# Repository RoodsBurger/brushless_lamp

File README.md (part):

# Brushless Lamp

Kinetic smart lamp. A BLDC gimbal motor raises / lowers a lit core to control
brightness; CCT LEDs ride with the core. A single rotary-encoder knob with push-
button drives everything locally; Matter over WiFi exposes the lamp to Apple
Home / Google Home / SmartThings. Production hardware is the **Seeed XIAO
ESP32-S3** running ESP-IDF + esp-matter; the chip handles the SimpleFOC v2.4.0
FOC loop itself on a dedicated core while WiFi, BLE, and CHIP share the other.

## Production build → [`s3/README.md`](s3/README.md)

That doc is the source of truth for everything current: BOM, wiring, toolchain,
build + flash, per-device Matter provisioning, code architecture, troubleshooting,
and the diagnostic story for the external-5 V boot path (see § 7.1). Start there.

## Repo layout

```
s3/                  Current build (XIAO ESP32-S3 + esp-matter)
  ├── firmware/      PRODUCTION — Matter ColorTemperatureLight
  ├── common/        Shared motor / pins / config
  ├── components/    Vendored SimpleFOC v2.4.0
  └── archive/       Dev history + diagnostic targets (none ship)
esp-idf/             Historical (XIAO ESP32-C6 build, frozen for rollback)
```

The C6 build below is kept verbatim only as a rollback reference.

---

## Historical (XIAO ESP32-C6, frozen for rollback)

The original BrushlessLamp build targeted the XIAO ESP32-C6 with arduino-esp32's
Matter library on top. It works, but Matter on C6 had several upstream bugs
(WiFi-reconnect crash, shared-default QR codes, etc.) that drove the migration
to the S3 + esp-matter stack documented in `s3/README.md`. The sections below
describe that older build and remain accurate for `esp-idf/`.

### Milestones — M1 + M2 + M3a + M3b + M4

Closed-loop **angular-position control** on the motor via an MT6701 ABZ encoder. A rotary encoder knob with push-button drives the user interface:
- **Position mode (default)**: knob turns the motor — the lit core rises/falls mechanically. Commanded position at 0 electrically turns the LEDs **off**.
- **Brightness mode**: knob adjusts LED brightness 0–100 % on a logarithmic curve.
- **Single click**: toggle between position and brightness mode.
- **Double click**: cycle motor speed preset `{10, 15, 20, 25}` rad/s.
- **Long-hold 5 s**: lamp LEDs pulse 5× as factory-reset warning.
- **Long-hold 9 s**: factory reset (clears Preferences, reboots).

`commanded`, `speed_idx`, `brightness`, and `cct` persist in flash. Boot applies a sensor_offset so the motor doesn't jump on startup.

### Hardware

- **MCU:** Seeed Studio XIAO ESP32-C6 (RISC-V, single HP core, WiFi 6, BLE 5, 802.15.4 for later Matter-over-Thread)
- **Driver:** SimpleFOC Mini (DRV8313; 3-phase, `IN1`/`IN2`/`IN3`/`EN` + `nSLEEP`/`nFAULT` + `U`/`V`/`W` phases)
- **Motor:** 4015 BLDC gimbal, 12–36 V, 11 pole pairs, hollow-shaft external rotor
- **Motor encoder:** MT6701 (ABZ mode, 1024 CPR)
- **User input:** PEC11-style rotary encoder with integrated push-button (20 detents/rev)
- **LED strip:** dual-channel CCT (common anode + warm-white cathode + cool-white cathode), driven at 24 V
- **LED switching:** 2× AO3400A N-channel logic-level MOSFETs (SOT-23), one per channel
- **Power:** Mean Well LRS-75-24 (24 V 3.2 A)
- **Buck:** Mini360 24 V → 5 V for the MCU

### Wiring

PWM + nSLEEP on D7–D10 (driver cluster), motor encoder A/B on D0/D1, rotary knob + push-button on D2–D4, LED MOSFET gates on D5/D6. All 11 broken-out GPIOs are used. EN is **hard-tied to 3V3 on the SimpleFOC Mini itself** — its pull-up is too weak to survive a floating MCU pin, and a lamp doesn't need software tri-state (`motor.disable()` still drives all three phases to 50 % duty, zero phase-to-phase differential, zero torque). nFAULT and Z are intentionally unconnected: stall detection covers faults, and Z only helps for single-turn absolute positioning which this project doesn't need.

| XIAO pin | Chip GPIO | Target | Notes |
|---|---|---|---|
| D10 | GPIO 18 | SimpleFOC Mini IN1 | PWM phase A (MCPWM) |
| D9  | GPIO 20 | SimpleFOC Mini IN2 | PWM phase B (MCPWM) |
| D8  | GPIO 19 | SimpleFOC Mini IN3 | PWM phase C (MCPWM) |
| D7  | GPIO 17 | SimpleFOC Mini nSLEEP | pulse LOW ≥ 30 µs to clear latched OCP/TSD |
| D6  | GPIO 16 | LED CW MOSFET gate | LEDC PWM 25 kHz, 10-bit |
| D5  | GPIO 23 | LED WW MOSFET gate | LEDC PWM 25 kHz, 10-bit |
| D0  | GPIO 0  | MT6701 A | quadrature, internal pull-up |
| D1  | GPIO 1  | MT6701 B | quadrature, internal pull-up |
| D2  | GPIO 2  | Rotary encoder A | PCNT ch0, hardware glitch-filtered |
| D3  | GPIO 21 | Rotary encoder B | PCNT ch1, hardware glitch-filtered |
| D4  | GPIO 22 | Rotary push button | INPUT_PULLUP, polled |
| 3V3 | — | MT6701 V+ · SimpleFOC Mini 3V3 · **EN jumper** · rotary encoder V+ | sourced from the XIAO's onboard LDO |
| GND | — | GND | common with Mean Well V−, Mini360 OUT−, and both LED MOSFET sources |
| 5V  | — | Mini360 OUT+ | XIAO power; onboard LDO then drives the 3V3 rail |
| — | — | Mean Well 24 V → Mini VCC / VM · LED strip VCC | motor rail + LED rail (shared 24 V) |

**Install a jumper from 3V3 to the EN header on the SimpleFOC Mini.** This is what keeps the DRV8313 enabled; without it the driver floats disabled.

#### Peripheral wiring (complete)

**Mean Well LRS-75-24 (24 V 3.2 A, mains-powered):**
- `V+` → SimpleFOC Mini `VM`, Mini360 `IN+`
- `V−` → SimpleFOC Mini `GND`, Mini360 `IN−`, XIAO `GND` (common)
- `L` / `N` / `⏚` → mains (respect mains safety: fused, enclosed, earth the chassis)

**Mini360 buck (24 → 5 V, trim set before connecting the XIAO):**
- `IN+` → Mean Well `V+`
- `IN−` → Mean Well `V−`
- `OUT+` → XIAO `5V`
- `OUT−` → XIAO `GND`

**SimpleFOC Mini (DRV8313 breakout):**
- `VM` → Mean Well `V+`
- `GND` → common ground
- `3V3` → XIAO `3V3` (logic rail + pull-ups)
- `IN1` → XIAO `D10`
- `IN2` → XIAO `D9`
- `IN3` → XIAO `D8`
- `EN` → **jumper to `3V3`** (on the breakout itself, not to the MCU)
- `nSLEEP` → XIAO `D7`
- `nFAULT` → not connected
- `U` / `V` / `W` (screw terminals) → motor phase wires. Initial phase order is a guess — if `initFOC` fails or the motor stutters, swap any two.

**MT6701 breakout (ABZ mode — verify the mode jumper matches this; the board ships in various configurations):**
- `V+` → XIAO `3V3`
- `GND` → common ground
- `A` pad (often labelled `DO` on the breakout's dual-purpose silk) → XIAO `D0`
- `B` pad (often labelled `CLK`) → XIAO `D1`
- `Z` pad (often labelled `CS`) → not connected

**Rotary encoder (PEC11-style, 5 pins — 3 on one side for the encoder, 2 on the other for the integrated push-button):**
- Encoder pin `A` → XIAO `D2`
- Encoder pin `B` → XIAO `D3`
- Encoder common (middle of the three) → `GND`
- Button pin 1 → XIAO `D4`
- Button pin 2 → `GND`
- (No external pull-ups needed — PCNT has a hardware glitch filter for A/B, and the button uses the MCU's `INPUT_PULLUP`.)

**LED MOSFET pair (AO3400A ×2, SOT-23, low-side switching, gate driven direct from 3V3 logic):**
- WW MOSFET: gate → XIAO `D5`, drain → LED strip `W` (warm-white cathode), source → `GND`
- CW MOSFET: gate → XIAO `D6`, drain → LED strip `C` (cool-white cathode), source → `GND`
- No gate resistor, pull-down, or flyback diode — same bare circuit as CylinderLamp. AO3400A is logic-level (Vgs(th) ≈ 0.9 V) and 3.3 V on the gate fully saturates it.
- Keep both MOSFET ground wires short and on the common GND rail; the 24 V LED return current flows through these sources.

**LED strip (dual-channel CCT, shared anode, 24 V):**
- `VCC` → Mean Well `V+` (24 V rail — tap the same distribution as the SimpleFOC Mini's `VM`)
- `W` (warm-white cathode) → WW MOSFET drain
- `C` (cool-white cathode) → CW MOSFET drain

### Build

```bash
arduino-cli compile --fqbn "esp32:esp32:XIAO_ESP32C6:CDCOnBoot=cdc,PartitionScheme=huge_app" arduino/BrushlessLamp/BrushlessLamp.ino
arduino-cli upload  --fqbn "esp32:esp32:XIAO_ESP32C6:CDCOnBoot=cdc,PartitionScheme=huge_app,EraseFlash=all" --port /dev/cu.usbmodem101 arduino/BrushlessLamp/BrushlessLamp.ino
```

`EraseFlash=all` is only required on the **first** flash after leftover partition state from another project (e.g. CylinderLamp). Subsequent uploads can drop it.

Requires arduino-esp32 core ≥ 3.0 (tested on 3.3.7) and the [SimpleFOC](https://github.com/simplefoc/Arduino-FOC) library (Library Manager → "Simple FOC", v2.4.x). On the C6, SimpleFOC selects the **MCPWM** backend automatically — you should see `SimpleFOC: compiling for ESP32 MCPWM driver` in the build output.

### Serial monitor

```bash
arduino-cli monitor --port /dev/cu.usbmodem101 --config baudrate=115200 --config dtr=off --config rts=off
```

**Don't omit `dtr=off` and `rts=off`** — on the XIAO ESP32-C6's USB-Serial/JTAG (same quirk as the C3 SuperMini), the default `dtr=on,rts=on` holds the chip in reset, so the sketch never runs while the monitor is attached. Symptom: connects cleanly, no banner ever appears.

### User gestures

The knob has two modes; single click toggles between them. The **measured shaft angle** acts as a position-proportional lamp gate: below 0.5 rad the LEDs are fully off, above 3 rad they run at the configured `brightness`, and in between they ramp linearly. Motion speed = fade speed — since the motor's trapezoidal profile makes shaft_angle move smoothly, the lamp fades in and out at whatever pace the motor is travelling.

| Gesture | Position mode (default) | Brightness mode |
|---|---|---|
| Turn knob CW | `commanded` += `RAD_PER_CLICK`, motor seeks | `brightness` +1 % |
| Turn knob CCW | `commanded` −= `RAD_PER_CLICK`, clamped at 0; the LEDs dim as the motor passes back through the 3 → 0.5 rad fade zone and go off below 0.5 rad | `brightness` −1 %, clamped at 0 |
| Single click | Switch to brightness mode | Switch to position mode |
| Double click | Advance motor speed preset (cycles `{10, 15, 20, 25}` rad/s) | Same |
| Hold ≥ 5 s | LEDs pulse 5× as factory-reset warning (~2.4 s) | Same |
| Hold ≥ 9 s | Factory reset — clears `Preferences`, reboots | Same |

`commanded`, `speed_idx`, `brightness`, and `cct` all persist via ESP32 `Preferences`. Knob mode itself is not persisted — every boot starts in position mode. On boot the firmware applies a `sensor_offset` so `shaft_angle` reads as the persisted `commanded`, the motor stays put, and LEDs illuminate at the saved brightness/CCT if `commanded > 0.1 rad`.

### Matter (M4)

The lamp is a **Matter ColorTemperatureLight** — one endpoint exposing OnOff, LevelControl, and ColorControl clusters. Controllers (Google Home, Apple Home, Alexa, Home Assistant) see it as a smart light with on/off, a brightness slider, and a color-temperature slider.

**Mapping to the physical lamp:**
- **On/Off** → `commanded` snaps to `POS_MIN` when off; restores the last Matter-level position when on.
- **Brightness (1..254)** → motor **position** (`commanded = brightness × POS_MAX / 254`). The LED gate then fades the lamp in as the motor passes through its 0.5 → 3 rad zone, same as the knob-driven path.
- **Color temperature (100–500 mireds)** → LED CCT mix (100 mireds = cool = `cct=100` = all CW; 500 mireds = warm = `cct=0` = all WW).

**LED brightness is deliberately knob-only** and not exposed to Matter. The Matter brightness slider is the motor slider; the lamp's own dimmer stays local on the knob.

**Commissioning:**
- On first boot the serial log prints `=== Matter: uncommissioned ===` followed by a QR-code URL and an 11-digit manual pairing code. Open Google Home → Add device → Matter-enabled device → scan the QR or type the manual code.
- **The motor + FOC ISR stays cold until the device is commissioned.** This keeps the 500 Hz SVPWM ISR from competing with the SPAKE2+ exchange on the single-core C6, which was the dominant cause of mid-commissioning panics. Once `Matter.isDeviceCommissioned()` flips true, the motor brings itself up automatically ~3 s later (after the BLE/WiFi handover settles). Already-paired devices skip the wait and init the motor immediately at boot.
- **Bench-test escape**: short-click the knob while uncommissioned to bring the motor up before pairing — useful for verifying the mechanical setup without a controller.
- BLE is **kept resident** post-commissioning. Earlier builds released it 3 s after pairing (saved ~60 KB heap), but the arduino-esp32 Matter library's WiFi-reconnect path on C6 dereferences the released memory and panics. Net cost: ~60 KB permanent heap, which the C6 can afford.
- The long-hold factory reset (9 s button press) both wipes `Preferences` and calls `Matter.decommission()` — the device re-appears as uncommissioned on next boot.

**Transport:** Matter-over-WiFi (which the arduino-esp32 Matter library picks for the XIAO C6 build by default). The C6 has the 802.15.4 radio for Matter-over-Thread too, but the arduino-esp32 Matter stack currently ships WiFi-configured for C6 — migrating to Thread is a follow-up (requires a custom build config; defer until needed).

**Known limitations:**
- **All flashed boards share the same QR code** — the arduino-esp32 Matter library doesn't expose a runtime API for per-device discriminator/passcode, so without patching the library or moving to full ESP-IDF every board presents identical commissioning credentials. Fine for a single-lamp household; would need addressing before any fleet deployment.
- **Consequence of the shared credentials**: if you already have a CylinderLamp (or another device built with the same arduino-esp32 Matter library defaults) commissioned in your Matter fabric, **decommission it before adding a new BrushlessLamp** — the commissioner will time out at the network step because it thinks the incoming device is a duplicate of the existing node. Symptom: commissioning gets as far as the BLE handshake, then fails with `Failsafe timer expired` and a `Cluster 0x0031 not found` line in the device's serial log.
- Devices appear as "Unverified" in the Home app because we don't carry a CSA-signed DAC. Harmless for personal use.

**FOC runs on a hardware timer ISR now** (500 Hz `hw_timer_t`). `motor.loopFOC()` no longer runs in `loop()` — the timer keeps SVPWM locked to the rotor regardless of Matter / Thread / BLE scheduler activity. `motor.move()` still runs in `loop()` and is tolerant of occasional ~4 ms scheduler preemption spikes (visible as `maxLp` jumps in the status line). 500 Hz still gives ~11 SVPWM updates per electrical cycle at the 25 rad/s top preset (11 pp × 25 rad/s ≈ 44 Hz electrical), and halving the ISR rate vs the prior 2 kHz / 1 kHz attempts leaves more headroom for the CHIP/WiFi tasks on the single-core C6.

**Outbound state syncs back to Matter at 10 Hz** (down from the original 200 ms / 5 Hz limit) and is wrapped in `chip::DeviceLayer::PlatformMgr().LockChipStack()` so we don't race the CHIP event-loop task's own attribute writes during inbound commands. A `bool btInUse(void) { return true; }` weak override at the top of the sketch keeps the arduino-esp32 core from auto-tearing the BT controller during the BLE → WiFi handover.

### Serial commands

- `G<float>` — goto absolute position in rad (clamped to `[POS_MIN, POS_MAX]`).
- `T<float>` — set `motor.velocity_limit` in rad/s (overrides the current speed preset until next double-click or reboot).
- `C<float>` — current limit, A (voltage-mode clamp; no shunt on DRV8313).
- `P<float>` — `motor.PID_velocity.P` gain.
- `I<float>` — `motor.PID_velocity.I` gain.
- `F<float>` — `motor.LPF_velocity.Tf` for velocity filtering, s.
- `R<float>` — phase resistance, Ω.
- `K<float>` — KV rating, rpm/V.
- `M<int>`   — motion downsample (PID runs every N `loopFOC` calls).
- `A<float>` — trapezoidal accel cap, rad/s² (how quickly `target` can change velocity during a seek).
- `B<int>`   — LED brightness 0..100 (applied through a gamma LUT, persisted).
- `W<int>`   — CCT mix 0..100 (0 = all warm-white, 100 = all cool-white; persisted, not touched by the knob — intended for Matter later).
- `X`        — reset driver (pulses nSLEEP to clear latched fault).

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
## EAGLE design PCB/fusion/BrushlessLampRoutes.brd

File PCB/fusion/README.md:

# Fusion / EAGLE schematic — `BrushlessLamp.sch`

A self-contained **EAGLE 9.x schematic** (the format Autodesk Fusion's Electronics
editor reads) with **every component instantiated, the full netlist wired, and a
footprint on every part**. The six key parts use the **official vendor symbols +
footprints** (SnapMagic `.lbr` files in [`../components/`](../components)); everything
else uses generic-but-standard footprints. Generated by
[`generate_sch.py`](generate_sch.py).

- **71 parts**, **6 libraries**, **57 nets**, ~230 pin-connections — the whole board.
- Verified against the generated file: 0 part/pin/net errors, 0 single-pin nets.

## Official vendor parts now baked in (no Replace needed)

| Part | Vendor library used | Notes |
|---|---|---|
| `U_MCU` | **ESP32-S3-WROOM-1-N8R8** | real Espressif land pattern + antenna keep-out; `TXD0/RXD0` wired as `U0TXD/U0RXD` |
| `U_DRV` | **DRV8313PWPR** | `EN1/2/3`→`DRVEN`, `PGND1-3/COMPP/COMPN/!COMPO/EXP`→`GND` auto-wired |
| `J_USB` | **TYPE-C-31-M-12** | real HRO USB-C land; `DP1/DP2`=D+, `DN1/DN2`=D−, `SHIELD`=GND |
| `D_USB` | **USBLC6-2SC6** | real ST footprint |
| `Q_WW`,`Q_CW` | **AO3400A** | LED low-side FETs |

The earlier "verify WROOM-1 / USB-C land pattern" warning is **resolved** — those are now
the real vendor footprints. The source `.lbr` files live in `../components/` and are
embedded into the `.sch` at generate time (so the schematic is still self-contained).

## What's still on the generic BLLIB library (IPC-7351 footprints)
`U_BUCK` (LMR51430, SOT-23-6 — datasheet-verified pinout), `Q1` (P-FET, SOT-23), all
passives (0402–1210), diodes (SOD/SMA/SMB), the inductor, the fuse, tactile buttons, and
all the connectors (`J_PWR/J_MOTOR/J_SENSOR/J_KNOB/J_BTN/J_LED/J_PROG`, JST-XH + screw
terminals). These use **IPC-7351B nominal land patterns**, with every dimension tabulated
in **[`FOOTPRINTS.md`](FOOTPRINTS.md)** so each is verifiable. Four are part-specific and
flagged there to confirm against the exact component you buy (the two bulk caps, the
inductor, the tactile switch).

> We checked the open-source EAGLE libraries (SparkFun, triffid JST-XH, KF301) — they were
> unsuitable for these parts (the JST-XH lib shorts all pins to one net; KF301 lacks 3P/5P;
> SparkFun passives are value-indexed and miss odd values + bulk-cap cases). The IPC-7351
> generated footprints are the correct, verifiable choice here.

## Open / update in Fusion
> You already imported an earlier version — this is a **newer** `.sch`. Re-upload it
> (Data Panel → Upload) as a new version, or open a fresh Electronics design from it.

1. **Data Panel → Upload** → select `BrushlessLamp.sch` → Fusion creates/updates the
   Electronics design. (The 5 vendor libraries ride inside the file, so the WROOM-1 etc.
   come in automatically — no separate library import needed.)
2. Open it → you'll see all parts + nets. Run **ERC**: expect only minor notes (e.g.
   unrouted/airwire reminders, or supply-pin warnings on the named power nets) — not
   errors.
3. Generate the board (schematic → PCB), place, route (2-layer), DRC.

## Regenerate
```sh
cd PCB/fusion
python3 generate_sch.py    # reads ../components/*.lbr, rewrites BrushlessLamp.sch
```
Needs the five `.lbr` files in `../components/`. The script's `REPLACED` / `PARTS` /
`DEVSETS` tables are the human-readable netlist + which parts use which library.

## Caveat
Authored to the EAGLE DTD, validates as well-formed, and the embedded vendor libraries are
used verbatim — but it was **not round-tripped through Fusion here** (no app/license in
this environment). If Fusion is fussy on first open it'll be cosmetic (the generic boxes
aren't pretty) — the parts, footprints, and netlist are correct. Re-save once from Fusion
for a native-blessed file.

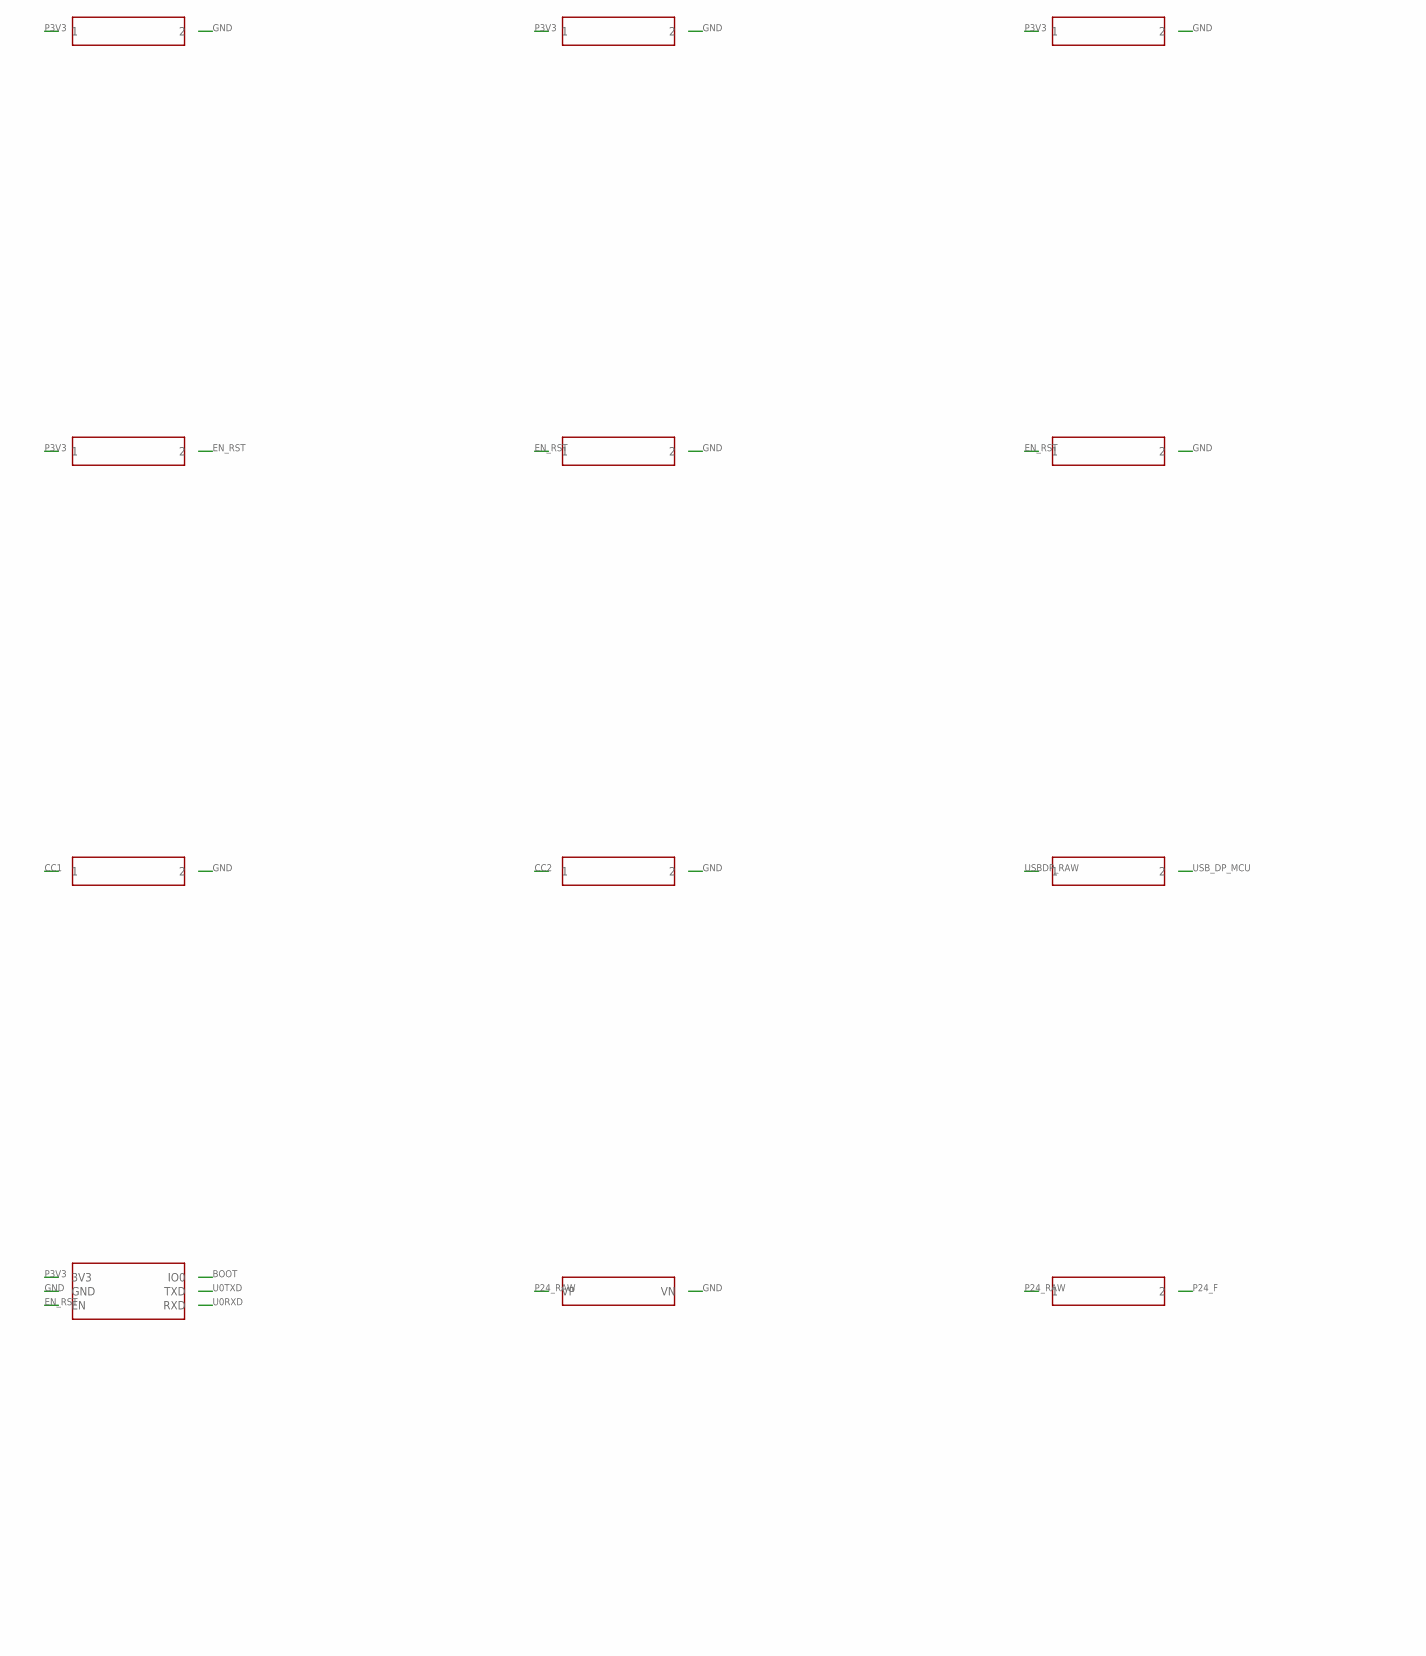
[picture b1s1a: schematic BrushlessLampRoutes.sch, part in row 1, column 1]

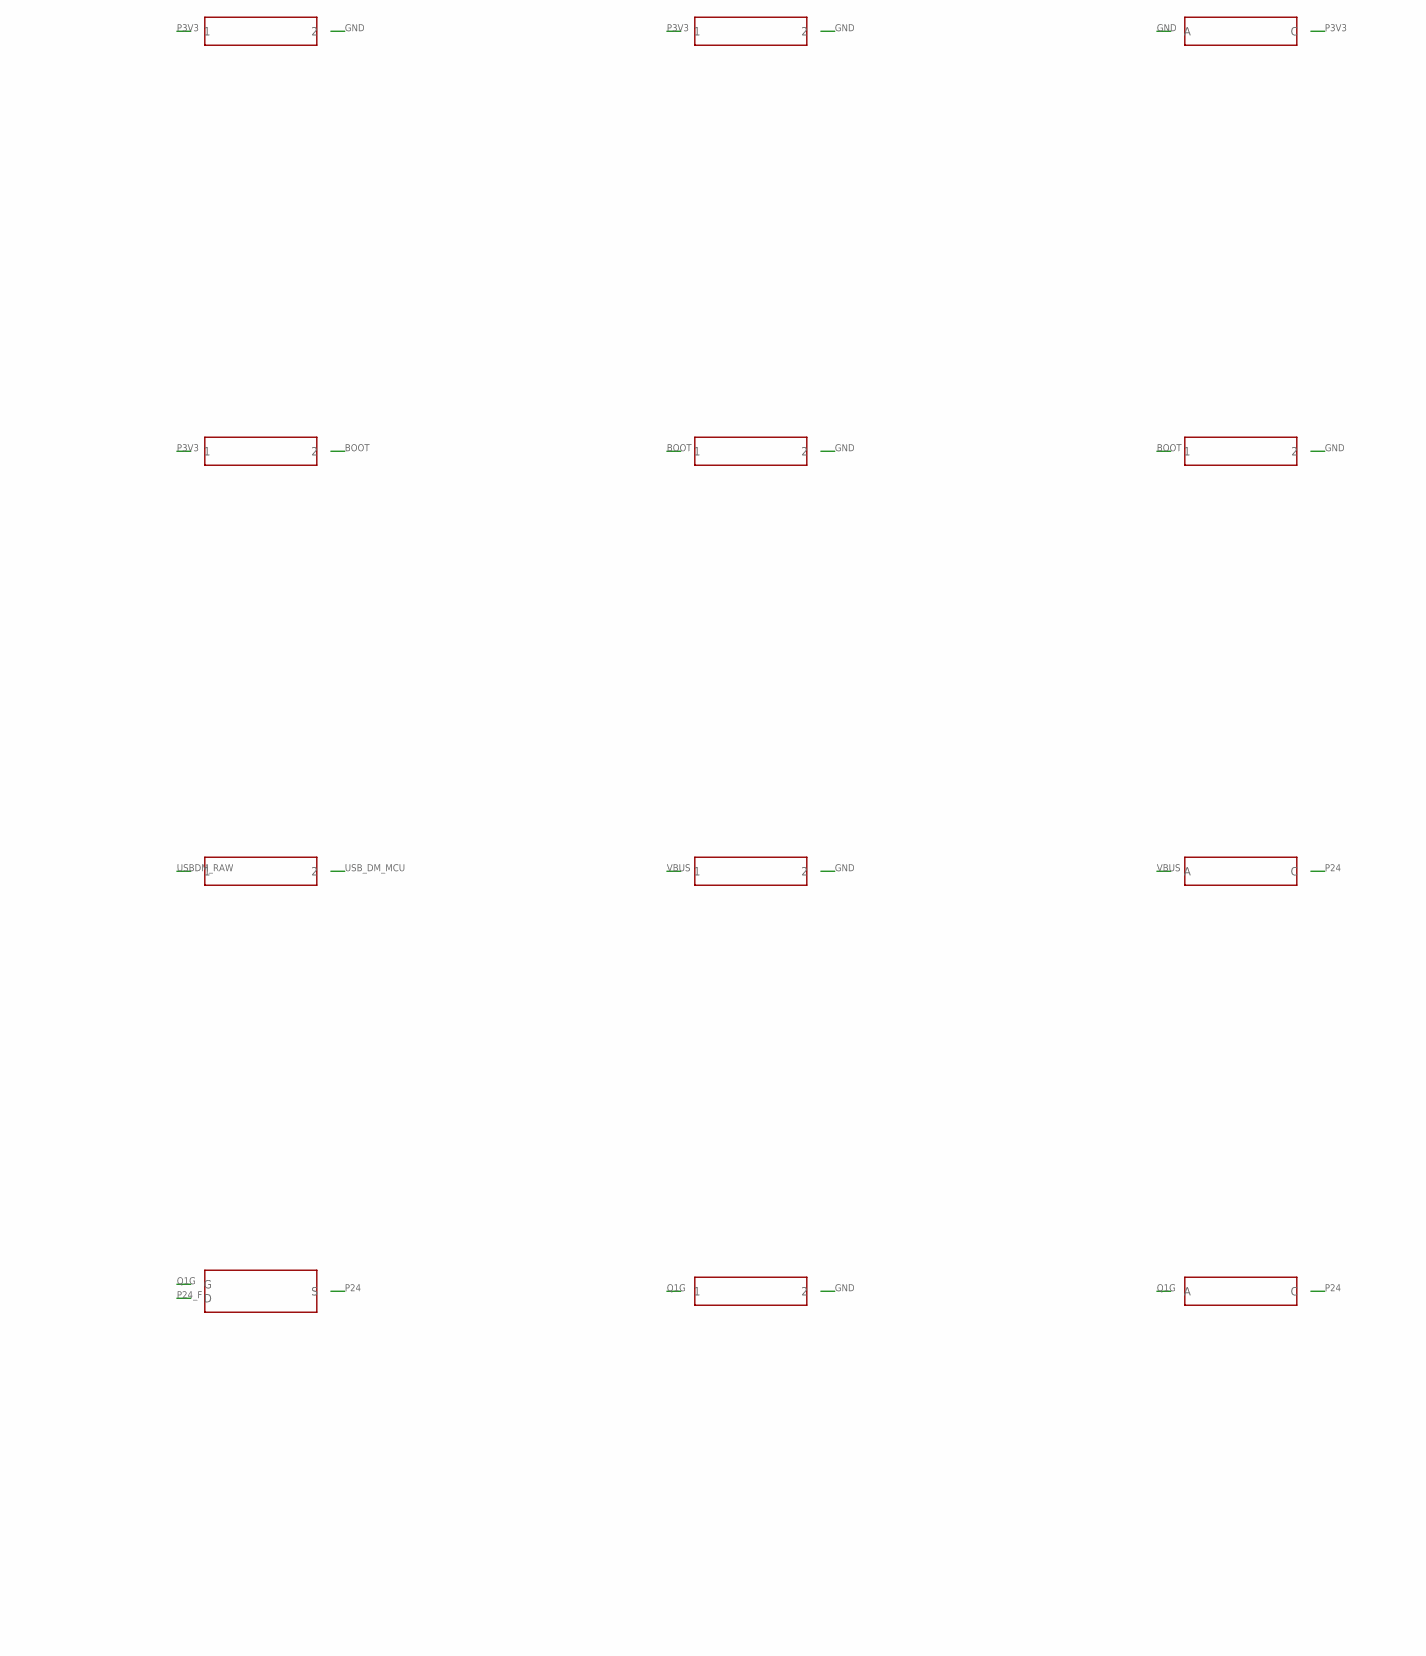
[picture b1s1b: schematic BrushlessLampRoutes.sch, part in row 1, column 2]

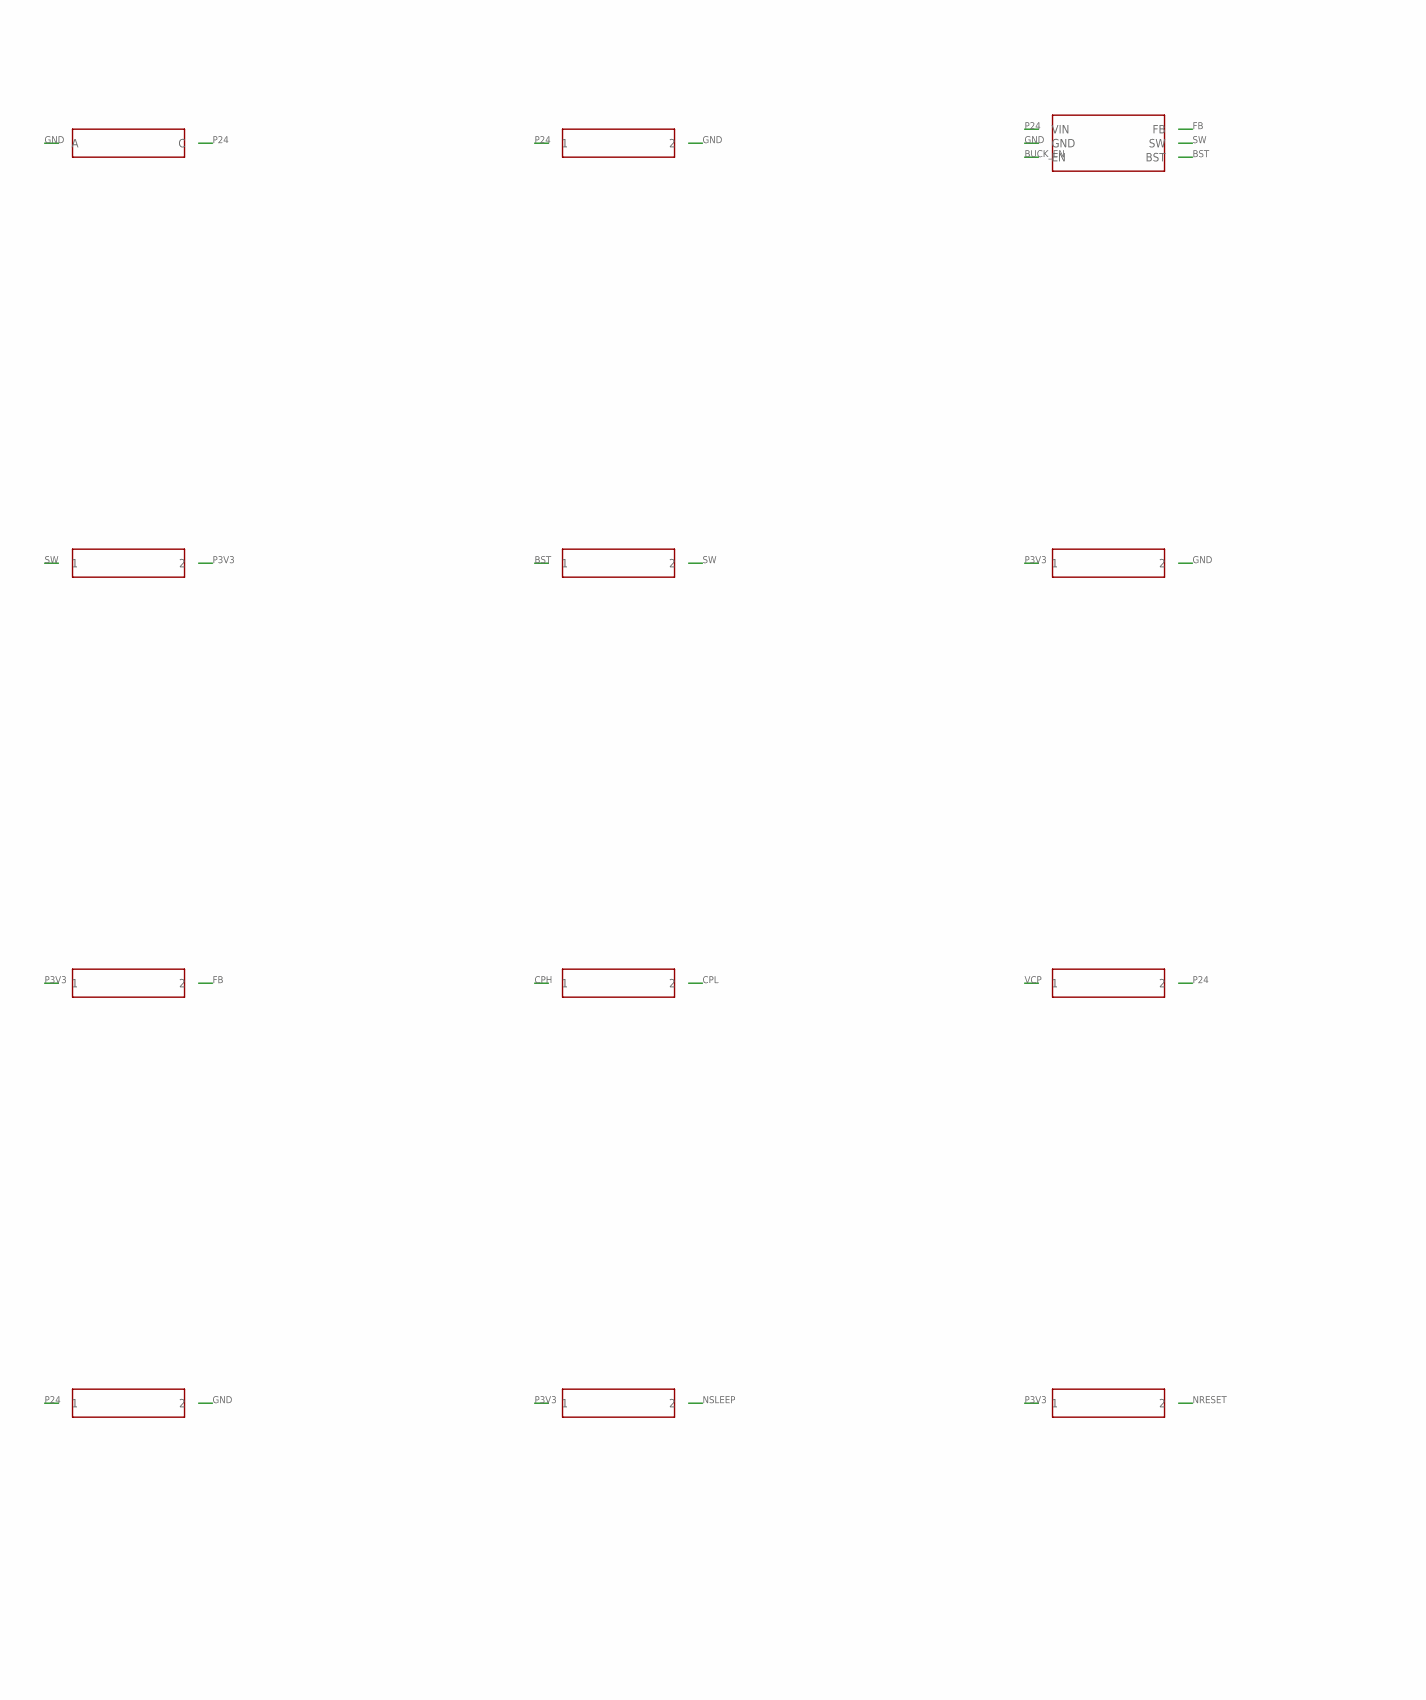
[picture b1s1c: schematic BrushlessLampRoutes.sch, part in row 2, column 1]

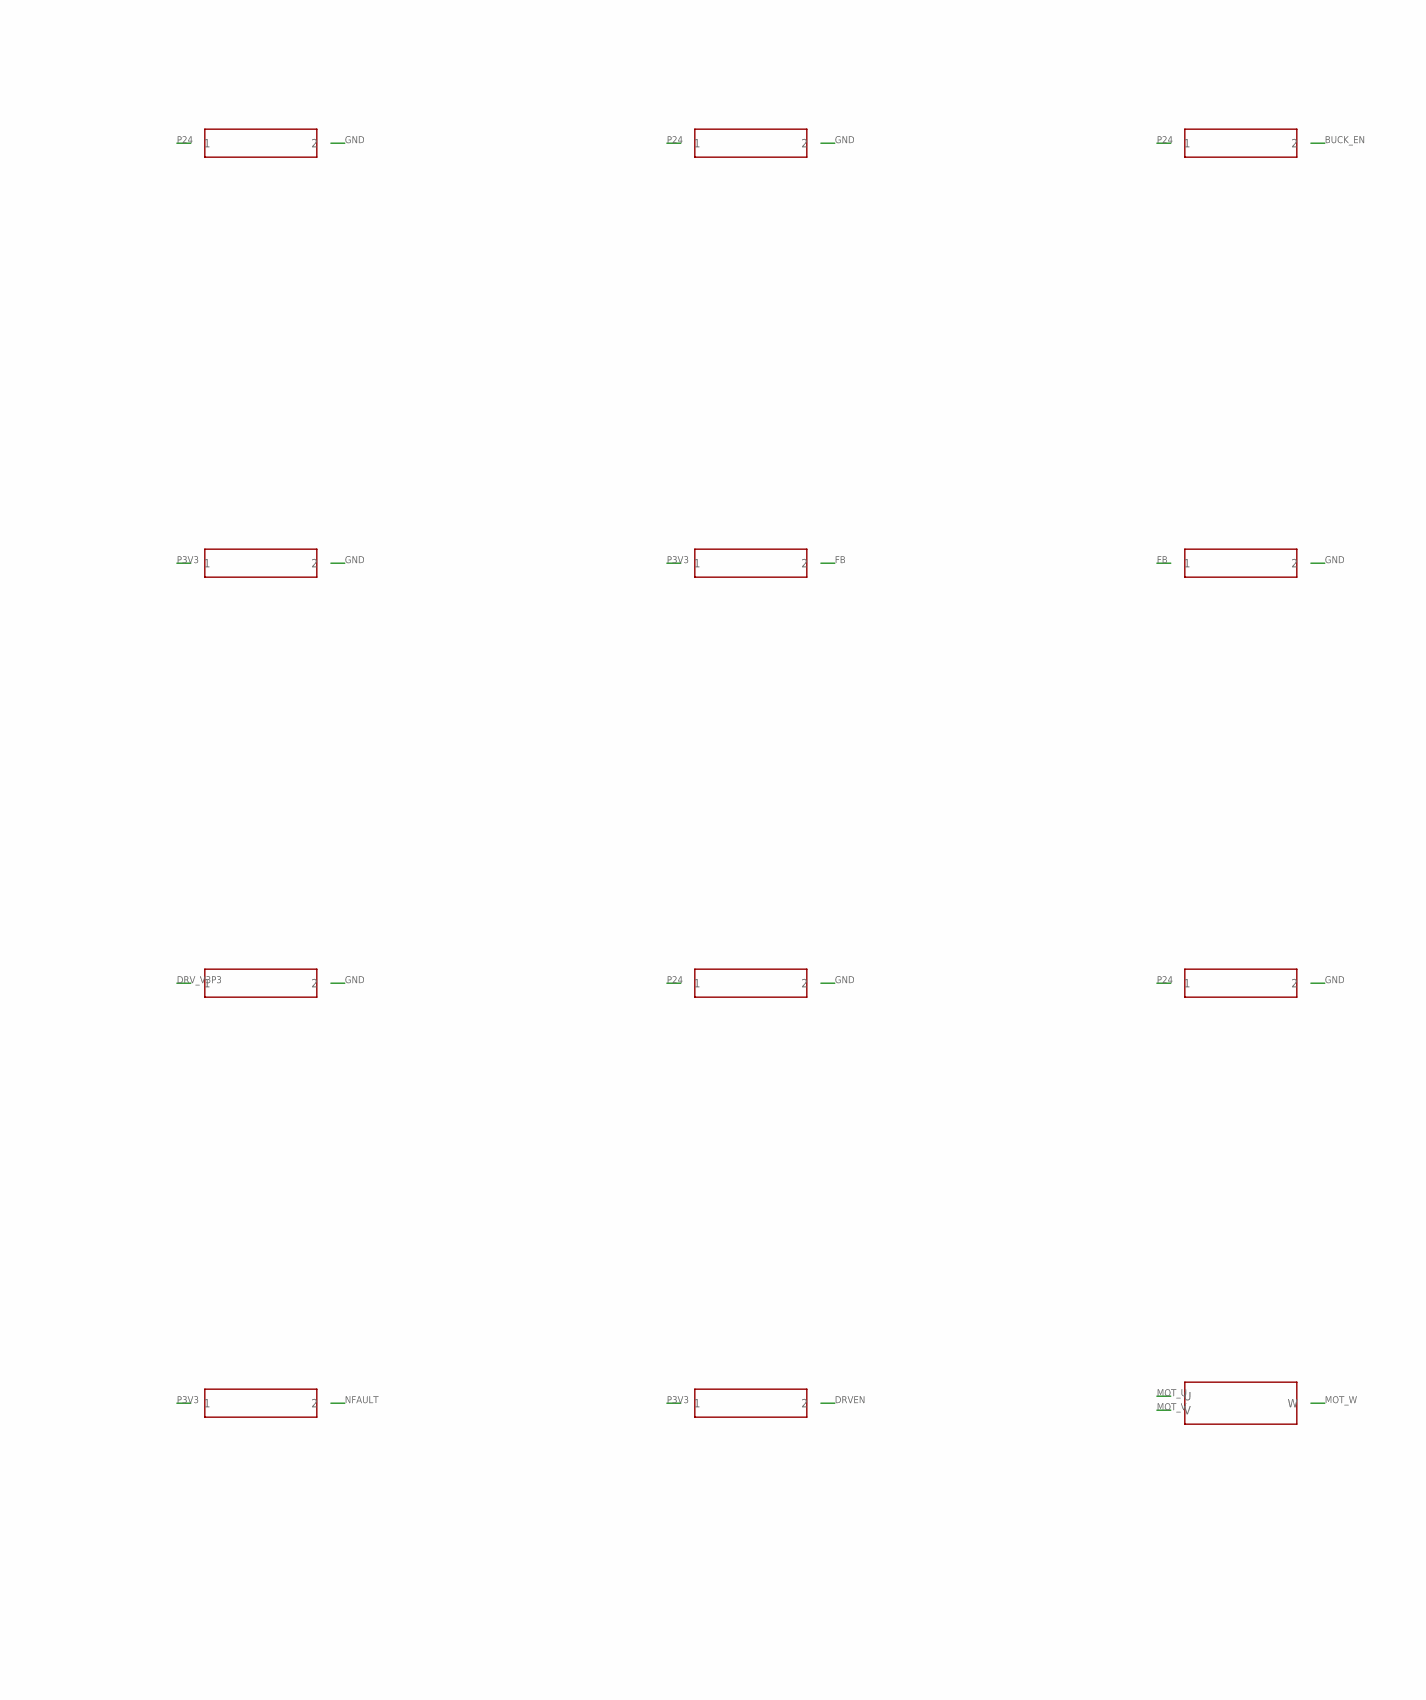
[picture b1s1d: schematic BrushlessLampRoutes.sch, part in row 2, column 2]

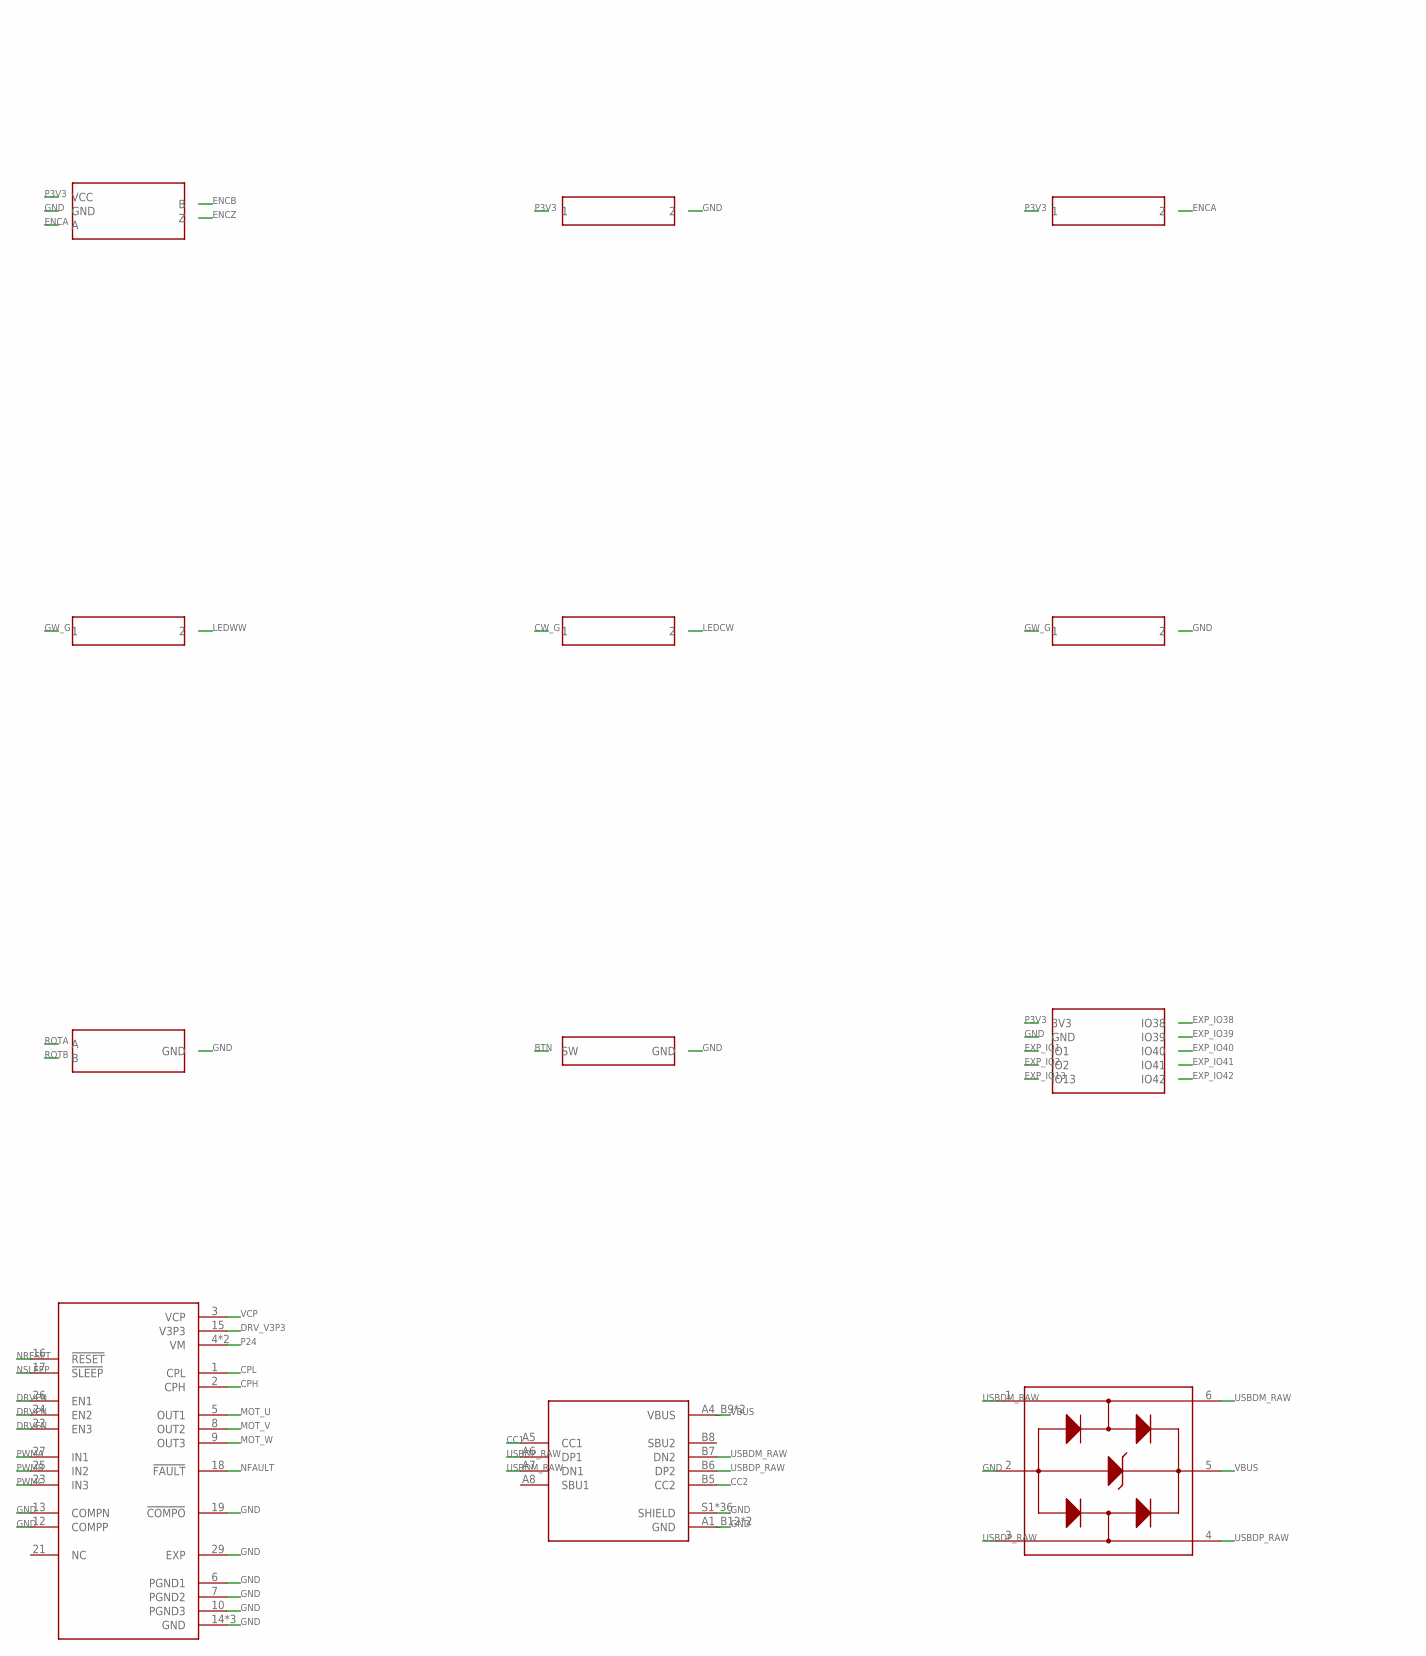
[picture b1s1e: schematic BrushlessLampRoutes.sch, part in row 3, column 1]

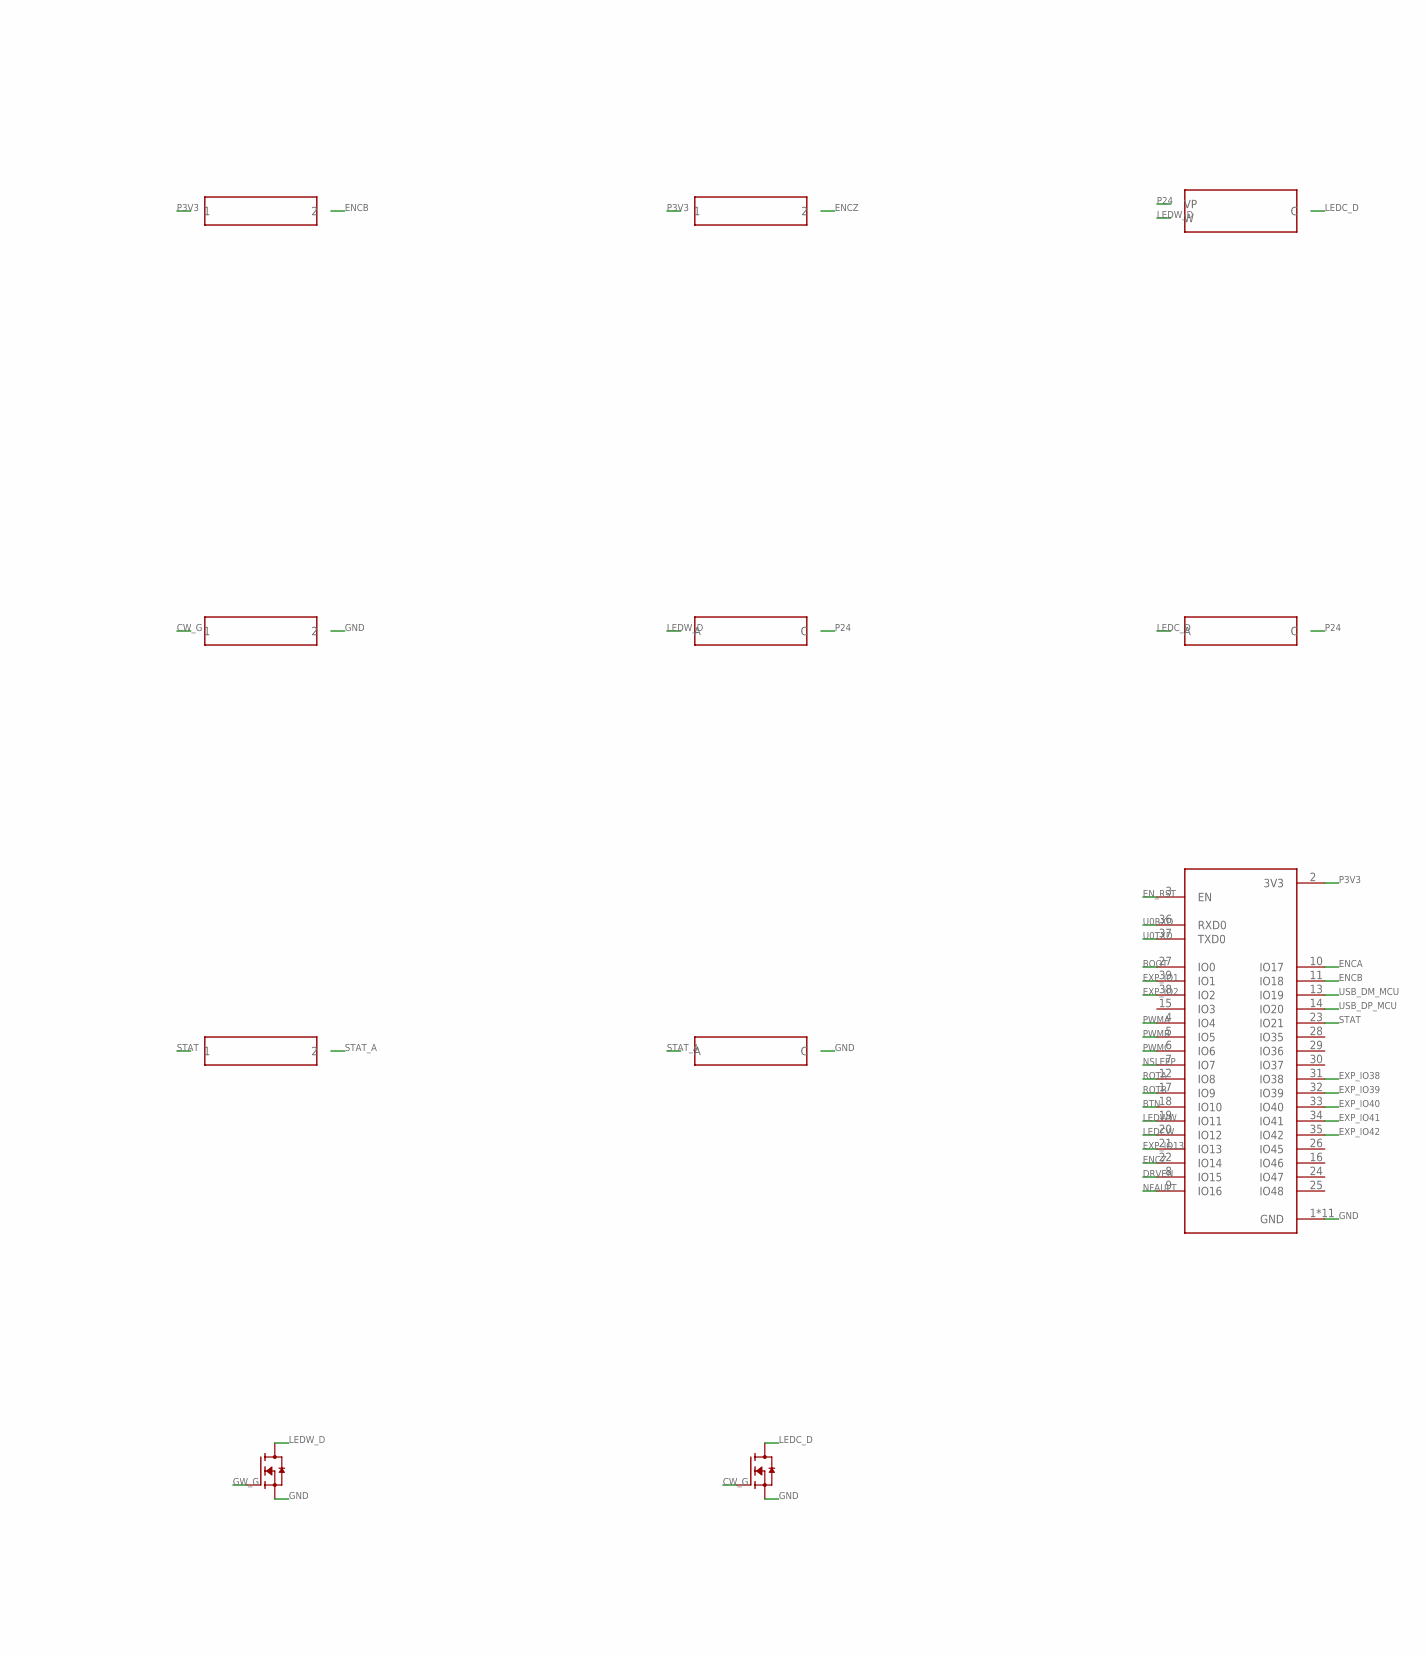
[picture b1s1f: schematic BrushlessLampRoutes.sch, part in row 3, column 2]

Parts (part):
C_BOOT: 100p; 0402
C_BOOT_B: 100n; 0402
C_CP: 10n; 0603
C_EN: 1u; 0603
C_FF: 22p; 0402
C_IN1: 10u-50V; 1210
C_IN2: 4.7u-50V; 1206
C_IN_BULK: 100u-50V; CAP_V
C_MCU1: 10u; 0805
C_MCU2: 1u; 0603
C_MCU3, C_MCU4: 100n; 0402
C_MCU_BULK: 470u; CAP_D
C_OUT1, C_OUT2: 22u; 0805
C_SENS: 100n; 0402
C_V3P3: 470n; 0603
C_VBUS: 4.7u; 0603
C_VCP: 100n; 0603
C_VM1, C_VM2: 100n-50V; 0603
C_VM_BULK: 100u-50V; CAP_V
D_CLC: clamp-DNP; SOD323
D_CLW: clamp-DNP; SOD323
D_MCU: ESD; SOD323
D_OR_USB: SS14; SMA
D_Q1: 10V-Zener; SOD123
D_USB: USBLC6-2SC6; SOT95P280X145-6N
F1: 2A; FUSENANO2
J_BTN: BUTTON; XH2
J_EXP: GPIO-EXP; HDR10
J_KNOB: KNOB; XH3
J_LED: CCT-STRIP; XH3
J_MOTOR: MOTOR; SCREW3
J_PROG: UART-FALLBACK; HDR6
J_PWR: 24V-IN; SCREW2
J_SENSOR: MT6701; SCREW5
J_USB: TYPE-C-31-M-12; HRO_TYPE-C-31-M-12
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
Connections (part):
BOOT: C_BOOT.1, J_PROG.4 (IO0), R_BOOT.2, SW_BOOT.1, SW_BOOT.2 (1), U_MCU.27 (IO0)
BST: C_BOOT_B.1, U_BUCK.6 (BST)
BTN: J_BTN.1 (SW), U_MCU.18 (IO10)
BUCK_EN: R_ENB.2, U_BUCK.5 (EN)
CC1: J_USB.A5 (CC1), R_CC1.1
CC2: J_USB.B5 (CC2), R_CC2.1
CPH: C_CP.1, U_DRV.2 (CPH)
CPL: C_CP.2, U_DRV.1 (CPL)
CW_G: Q_CW.1 (G), R_GC.1, R_PDC.1
DRVEN: R_EN_DRV.2, U_DRV.22 (EN3), U_DRV.24 (EN2), U_DRV.26 (EN1), U_MCU.8 (IO15)
DRV_V3P3: C_V3P3.1, U_DRV.15 (V3P3)
ENCA: J_SENSOR.3 (A), R_AZ_A.2, U_MCU.10 (IO17)
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
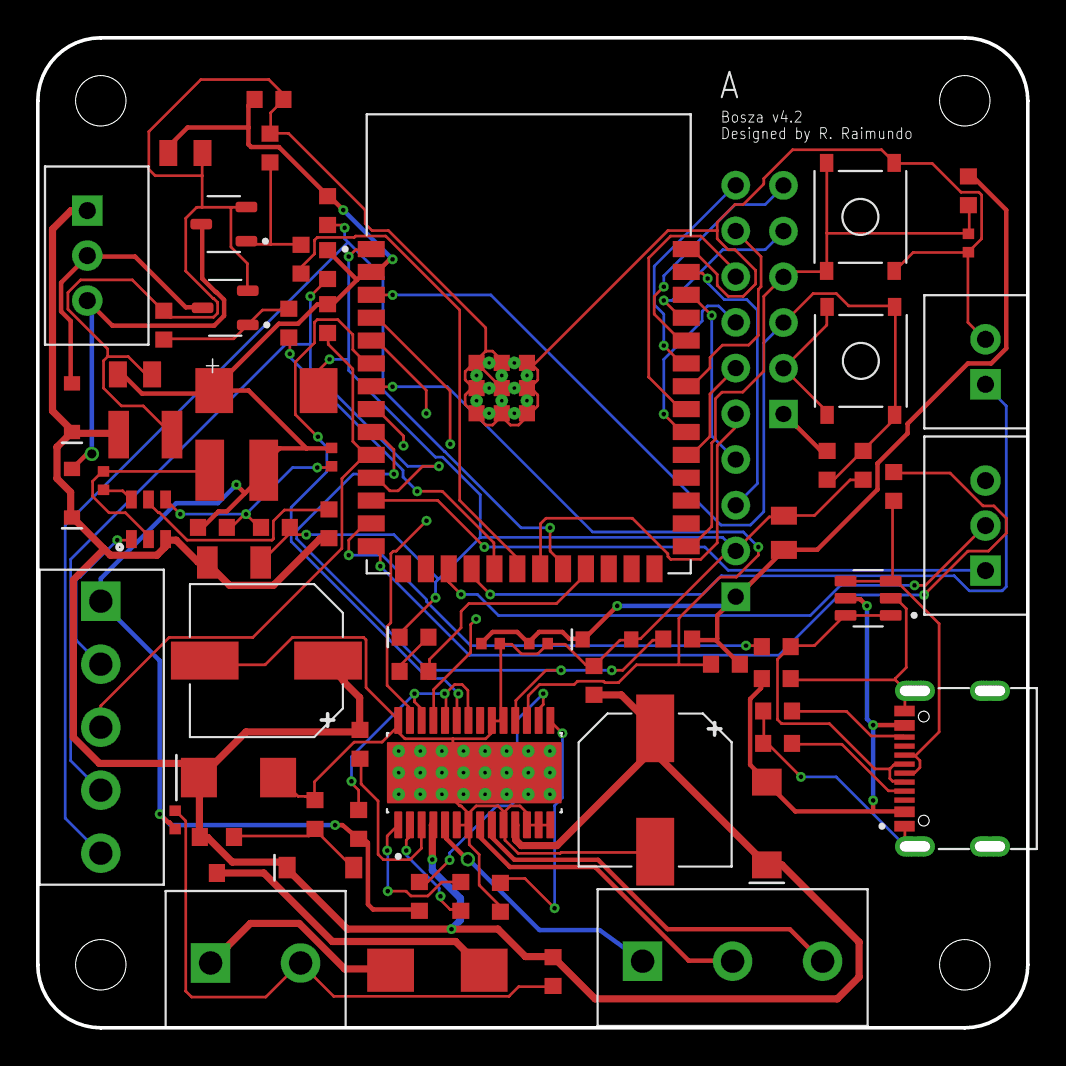
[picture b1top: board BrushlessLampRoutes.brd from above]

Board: 4 copper layers, 55.0 x 55.0 mm, 71 parts (0 on the bottom side), 57 nets.

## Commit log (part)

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2026-05-30 S3 firmware: add m1/m2/m3/m4 modules and esp-idf app_main scaffold
    Adds the ESP32-S3 development tree (s3/m1-motor, m2-knob, m3-leds, m4-matter,
    test_ble_arduino) and the native ESP-IDF + esp-matter entry point. Extends
    .gitignore to cover all of .claude/ and macOS Icon files.
2026-06-17 S3: release fw-1.0.1 (OTA version 10001)
2026-06-17 S3: release fw-1.0.2 (OTA version 10002)
2026-06-17 S3: release fw-1.0.3 (OTA version 10003)
2026-06-17 S3: release fw-1.0.4 (OTA version 10004)
2026-06-17 S3: release fw-1.0.5 (OTA version 10005)
2026-06-17 S3: release fw-1.1.0 (OTA version 10100)
2026-06-17 S3: release fw-1.2.0 (OTA version 10200)
2026-06-17 S3: release fw-1.2.1 (OTA version 10201)
2026-06-18 S3: release fw-1.2.2 (OTA version 10202)
2026-06-18 S3: release fw-1.2.3 (OTA version 10203)
